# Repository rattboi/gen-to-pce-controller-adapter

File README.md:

Simple Genesis 3-button to PC-Engine adapter
============================================

Tested on breadboard, test PCBs incoming

![PCB Front][pcb_front]

[pcb_front]: https://github.com/rattboi/gen-to-pce-controller-adapter/raw/master/images/3d-render.png "Front PCB"

Genesis Controller
==================

|Pin | Type | Name (Select=GND) | Name (Select=+5V) |
|----|------|-------------------|-------------------|
|1   | Out  | Up                | Up                |
|2   | Out  | Down              | Down              |
|3   | Out  | Gnd               | Left              |
|4   | Out  | Gnd               | Right             |
|5   |      | +5VDC             | +5VDC             |
|6   | Out  | Button A          | Button B          |
|7   | In   | Select            | Select            |
|8   |      | Ground            | Ground            |
|9   | Out  | Start             | Button C          |

PC-Engine Controller
====================

|Pin | Type | Name (Select=GND) | Name (Select=+5V) |
|----|------|-------------------|-------------------|
|1   |      | +5VDC             | +5VDC             |
|2   | Out  | Button C (I)      | Up                |
|3   | Out  | Button B (II)     | Right             |
|4   | Out  | Button A (Sel)    | Down              |
|5   | Out  | Start             | Left              |
|6   | In   | Select            | Select            |
|7   | In   | /Enable           | /Enable           |
|8   |      | Ground            | Ground            |

PC-Engine Extension Wiring
==========================

|Pin | Color |
|----|-------|
|1   | Brown |
|2   | Red   |
|3   | Orange|
|4   | Yellow|
|5   | Green |
|6   | Blue  |
|7   | Purple|
|8   | Black |

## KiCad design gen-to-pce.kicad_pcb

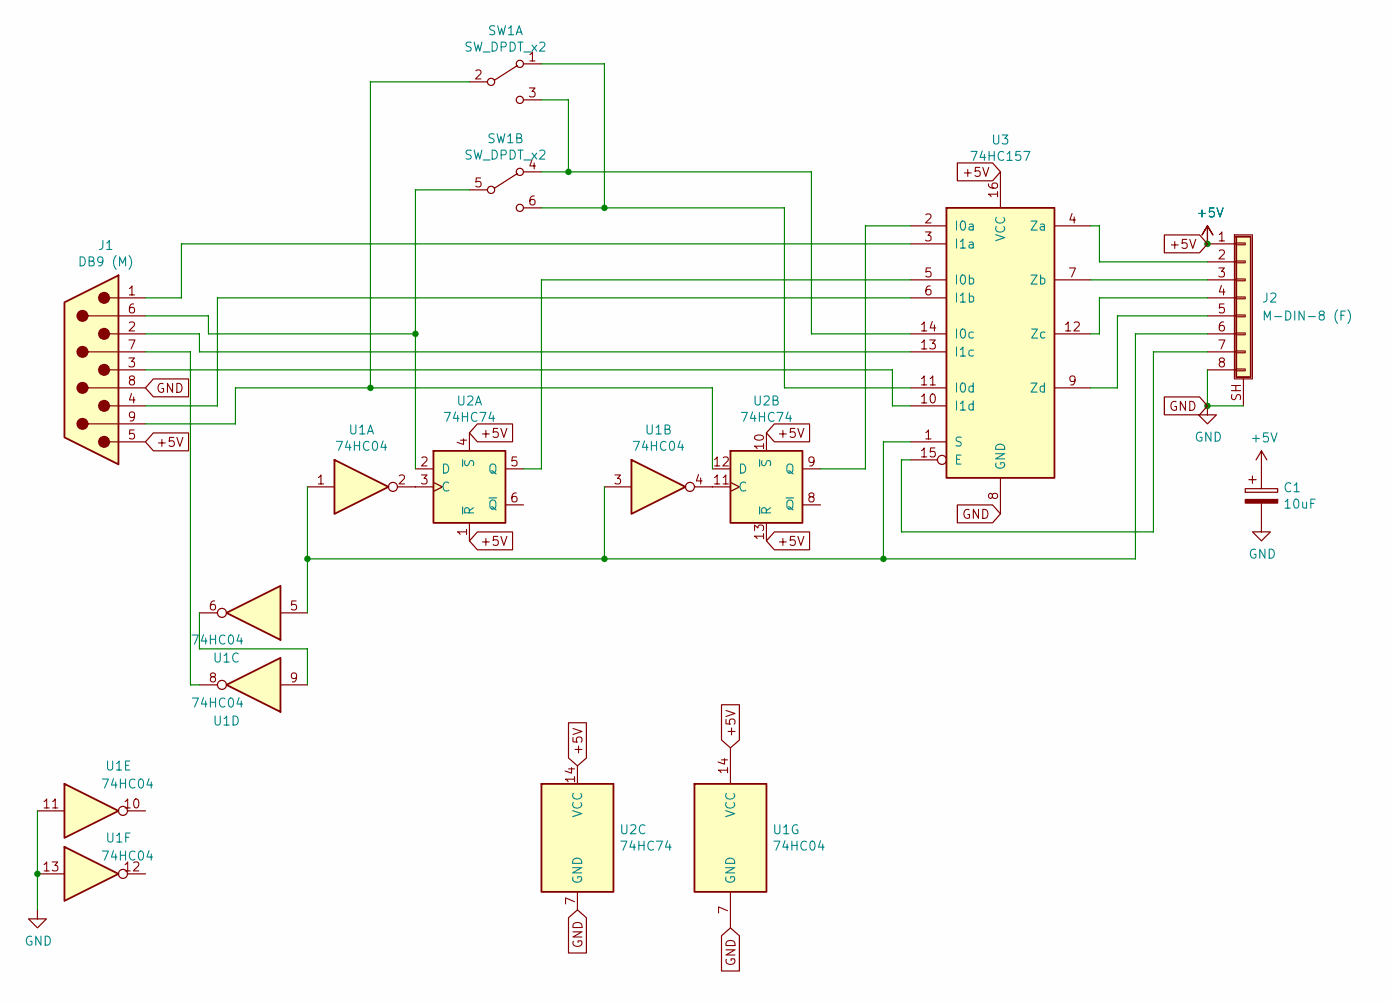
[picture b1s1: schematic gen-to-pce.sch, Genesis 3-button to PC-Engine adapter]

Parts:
C1: 10uF; CP_Radial_D5.0mm_P2.50mm
J1: DB9 (M); DSUB-9_Jack_5747840-3
J2: M-DIN-8 (F); minidin-8
SW1: SW_DPDT_x2; SW_E-Switch_EG2219_DPDT_Angled
U1: 74HC04; DIP-14_W7.62mm_LongPads
U2: 74HC74; DIP-14_W7.62mm_LongPads
U3: 74HC157; DIP-16_W7.62mm_LongPads

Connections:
+5V: C1.1, J1.5, J2.1, U1.14 (VCC), U2.1 (~R), U2.4 (~S), U2.10 (~S), U2.13 (~R), U2.14 (VCC), U3.16 (VCC)
GND: C1.2, J1.8, J2.8, J2.SH (Shield), U1.7 (GND), U1.11, U1.13, U2.7 (GND), U3.8 (GND)
unnamed: J1.1, U3.3 (I1a)
unnamed: J1.2, U3.13 (I1c)
unnamed: J1.3, U3.10 (I1d)
unnamed: J1.4, U3.6 (I1b)
unnamed: J1.6, SW1.5 (B), U2.2 (D)
unnamed: J1.7, U1.8
unnamed: J1.9, SW1.2 (B), U2.12 (D)
unnamed: J2.2, U3.4 (Za)
unnamed: J2.3, U3.7 (Zb)
unnamed: J2.4, U3.12 (Zc)
unnamed: J2.5, U3.9 (Zd)
unnamed: J2.6, U1.1, U1.3, U1.5, U3.1 (S)
unnamed: J2.7, U3.15 (E)
unnamed: SW1.1 (A), SW1.6 (C), U3.11 (I0d)
unnamed: SW1.3 (C), SW1.4 (A), U3.14 (I0c)
unnamed: U1.2, U2.3 (C)
unnamed: U1.4, U2.11 (C)
unnamed: U1.6, U1.9
unnamed: U2.5 (Q), U3.5 (I0b)
unnamed: U2.9 (Q), U3.2 (I0a)

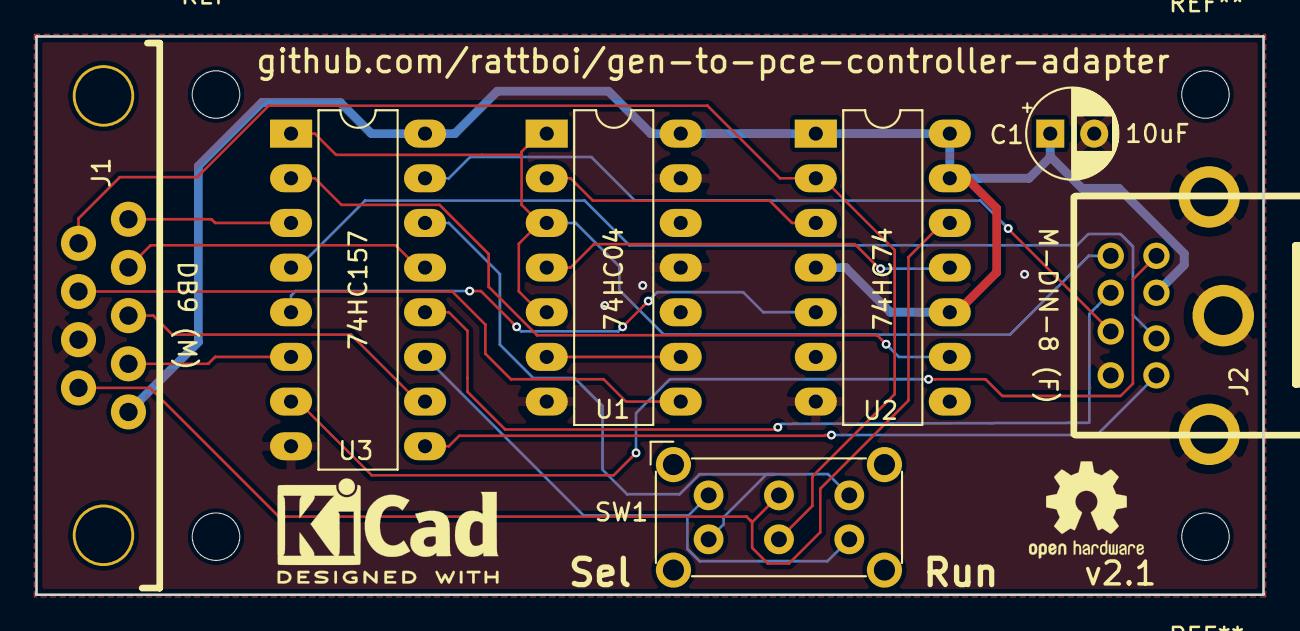
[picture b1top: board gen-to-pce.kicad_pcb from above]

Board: 2 copper layers, 69.8 x 31.8 mm, 7 parts (0 on the bottom side), 22 nets.

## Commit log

2018-09-04 Added some tables about the controller mappings
2018-09-06 Added extension cable color guide
2018-09-06 Fixed button swap B/C. Apparently PCE is II, then I
2018-09-08 First pass at PCB. Needs some work. I don't know what I'm doing, lol
2018-09-08 More silkscreen labels, better traces
2018-09-10 Ground fill, larger power traces, rectanglular edge cuts
2018-09-10 M-din-8 mount holes plated, select line delay
    Added select line delay for genesis controller to make sure there's no
    problem with propagation delay and setup time.
2018-09-11 Fixed up silkscreen, added oshw + kicad logos
2018-09-11 Added images to docs, fixed up docs a tiny (tiny) bit
2018-09-17 Archive modules, move J2 silkscreen onto pcb
2018-09-17 Add DPDT switch, reroute to account for switch
    The switch swaps the A button and Start button, which makes it the same
    as an Avenue Pad 3, basically. With the Avenue Pad 3, the extra button
    exists where the A button is on the Genesis, and the mapping is selected
    by a switch on the controller. Some games use III mapped to Sel, some
    use III mapped to Run.
    The original design had A (which you can consider III) hard-mapped to
2018-09-17 Added 3d render from kicad, removed Oshpark renders
    This one has the switch
2018-09-17 Newer 3d render
2018-09-17 Add III button (A on genesis) mapping to silkscreen
2018-09-18 Adding outline for pcb replacement (not really ready)
2018-09-24 Flip text around to match text on chips
2019-03-31 Update to v2.1, wider +5V traces, added decoupling cap
2019-03-31 Replace render with 2.1 version
